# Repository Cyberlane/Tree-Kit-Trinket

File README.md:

Tree-Kit-Trinket
================

Electronic PCB Kit with a Christmas twist

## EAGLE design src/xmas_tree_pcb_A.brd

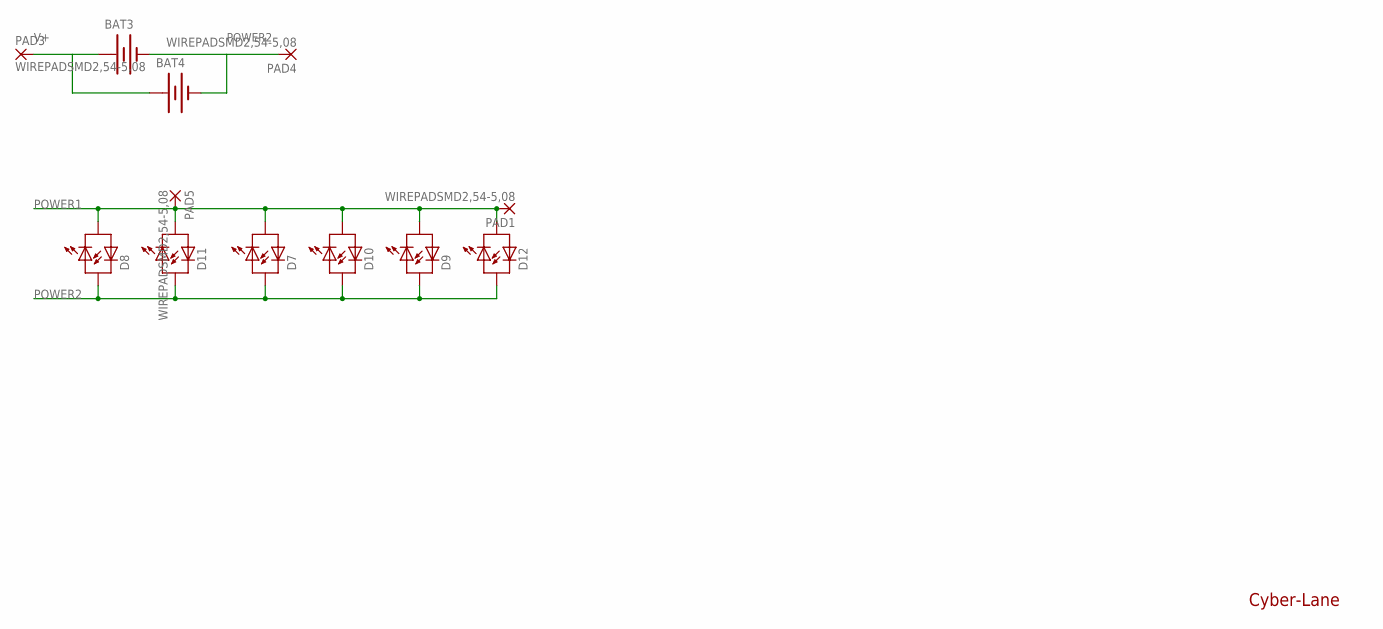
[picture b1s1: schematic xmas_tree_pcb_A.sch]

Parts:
BAT3, BAT4: BATTERY20PTH; BATTCOM_20MM_PTH
D7, D8, D9, D10, D11, D12: LED_BI_COLOR; LED3MM
PAD1, PAD3, PAD4, PAD5: WIREPADSMD2,54-5,08; SMD2,54-5,08

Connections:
POWER1: D7.K (C1), D8.K (C1), D9.K (C1), D10.K (C1), D11.K (C1), D12.K (C1), PAD1.1, PAD5.1
POWER2: BAT3.2 (-), BAT4.2 (-), D7.A (A1), D8.A (A1), D9.A (A1), D10.A (A1), D11.A (A1), D12.A (A1), PAD4.1
V+: BAT3.1 (+), BAT4.1 (+), PAD3.1

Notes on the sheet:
Cyber-Lane

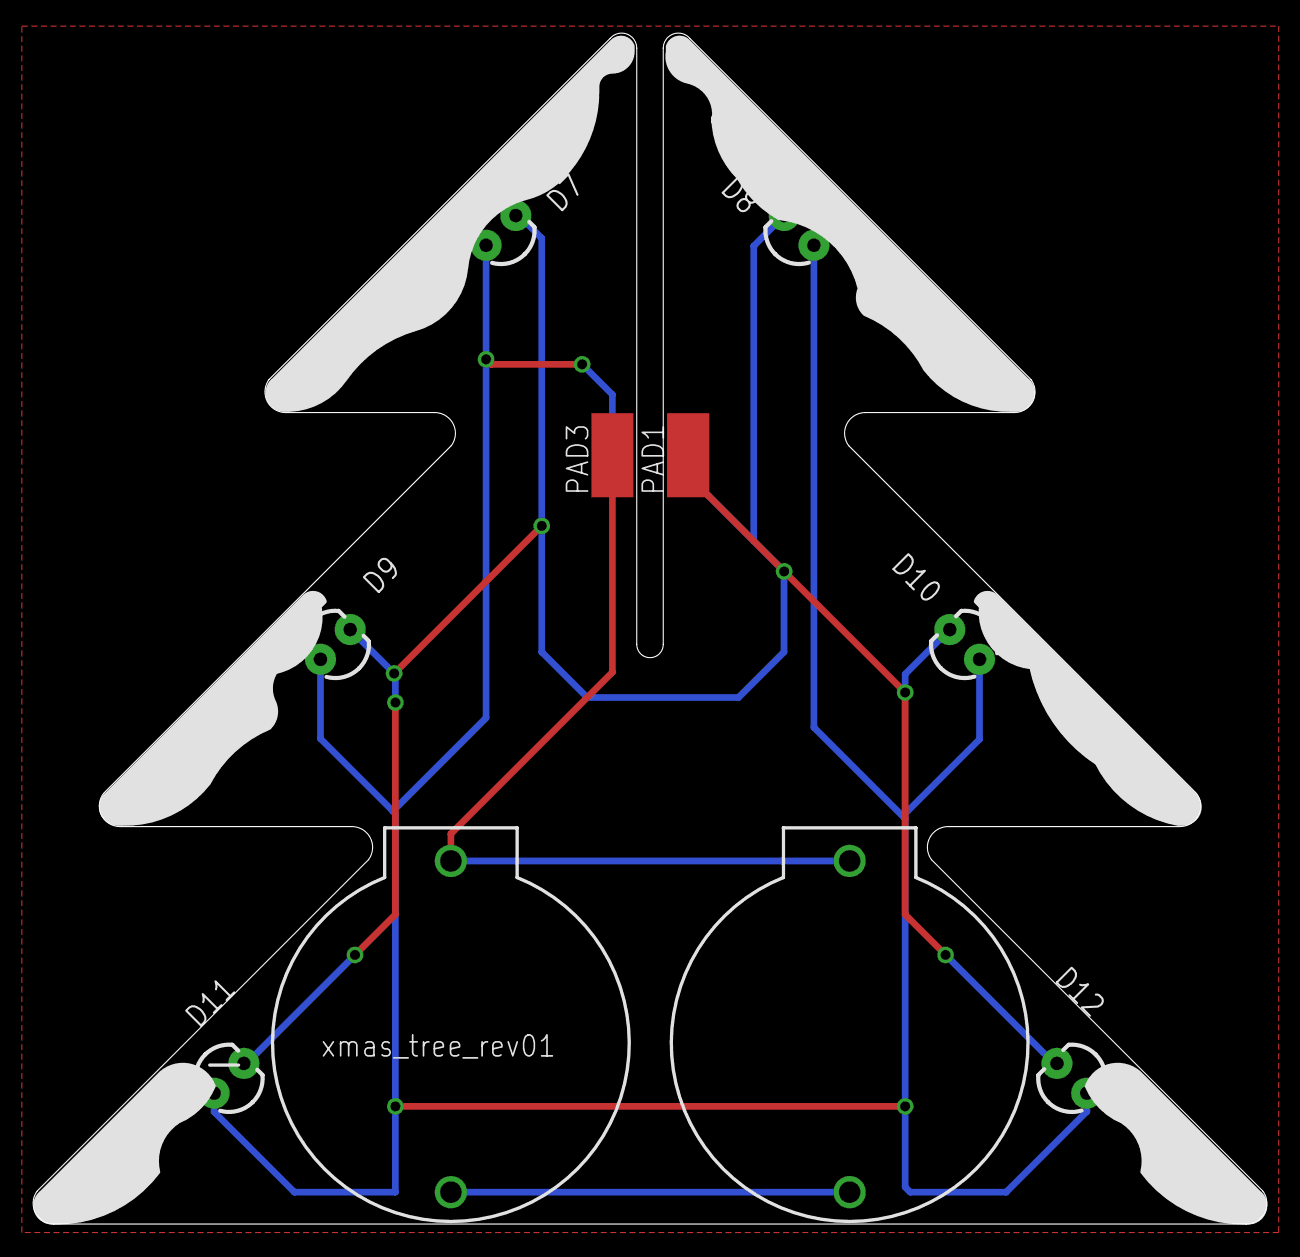
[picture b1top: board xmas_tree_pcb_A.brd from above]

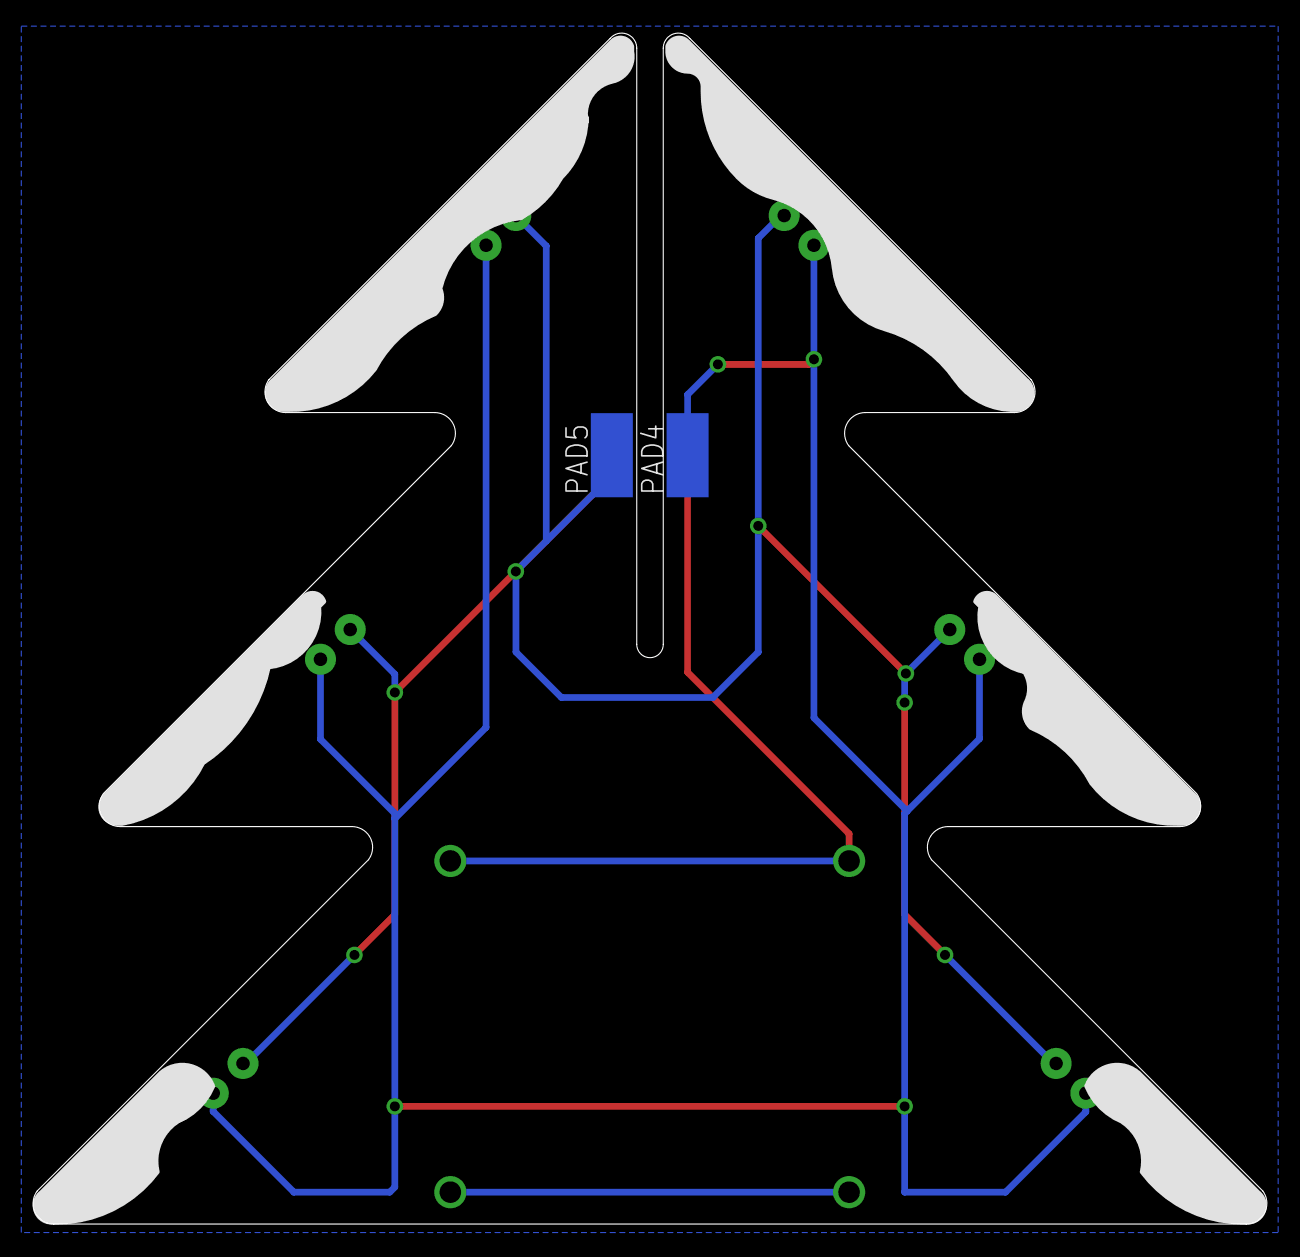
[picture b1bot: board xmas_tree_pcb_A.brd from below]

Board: 2 copper layers, 74.5 x 71.9 mm, 12 parts (2 on the bottom side), 3 nets.

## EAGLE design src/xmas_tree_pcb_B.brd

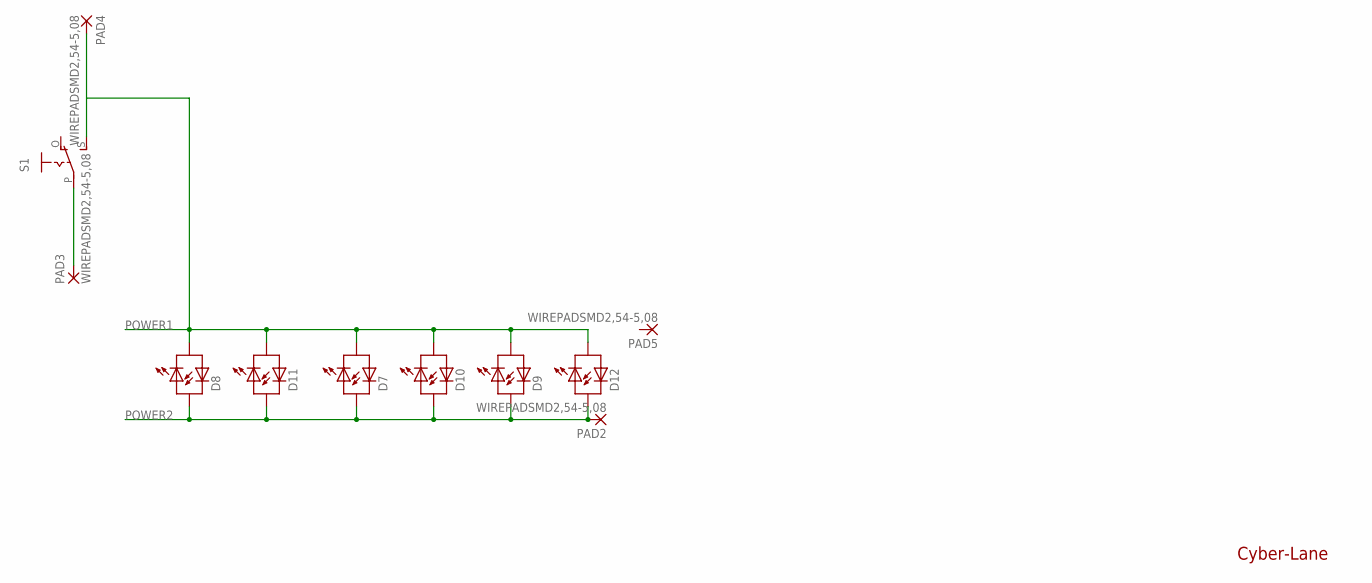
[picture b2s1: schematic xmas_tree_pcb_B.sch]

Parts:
D7, D8, D9, D10, D11, D12: LED_BI_COLOR; LED3MM
PAD2, PAD3, PAD4, PAD5: WIREPADSMD2,54-5,08; SMD2,54-5,08
S1: EG1218S; EG1218

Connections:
POWER1: D7.K (C1), D8.K (C1), D9.K (C1), D10.K (C1), D11.K (C1), D12.K (C1), PAD4.1, S1.S
POWER2: D7.A (A1), D8.A (A1), D9.A (A1), D10.A (A1), D11.A (A1), D12.A (A1), PAD2.1
V+: PAD3.1, S1.P

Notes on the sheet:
Cyber-Lane

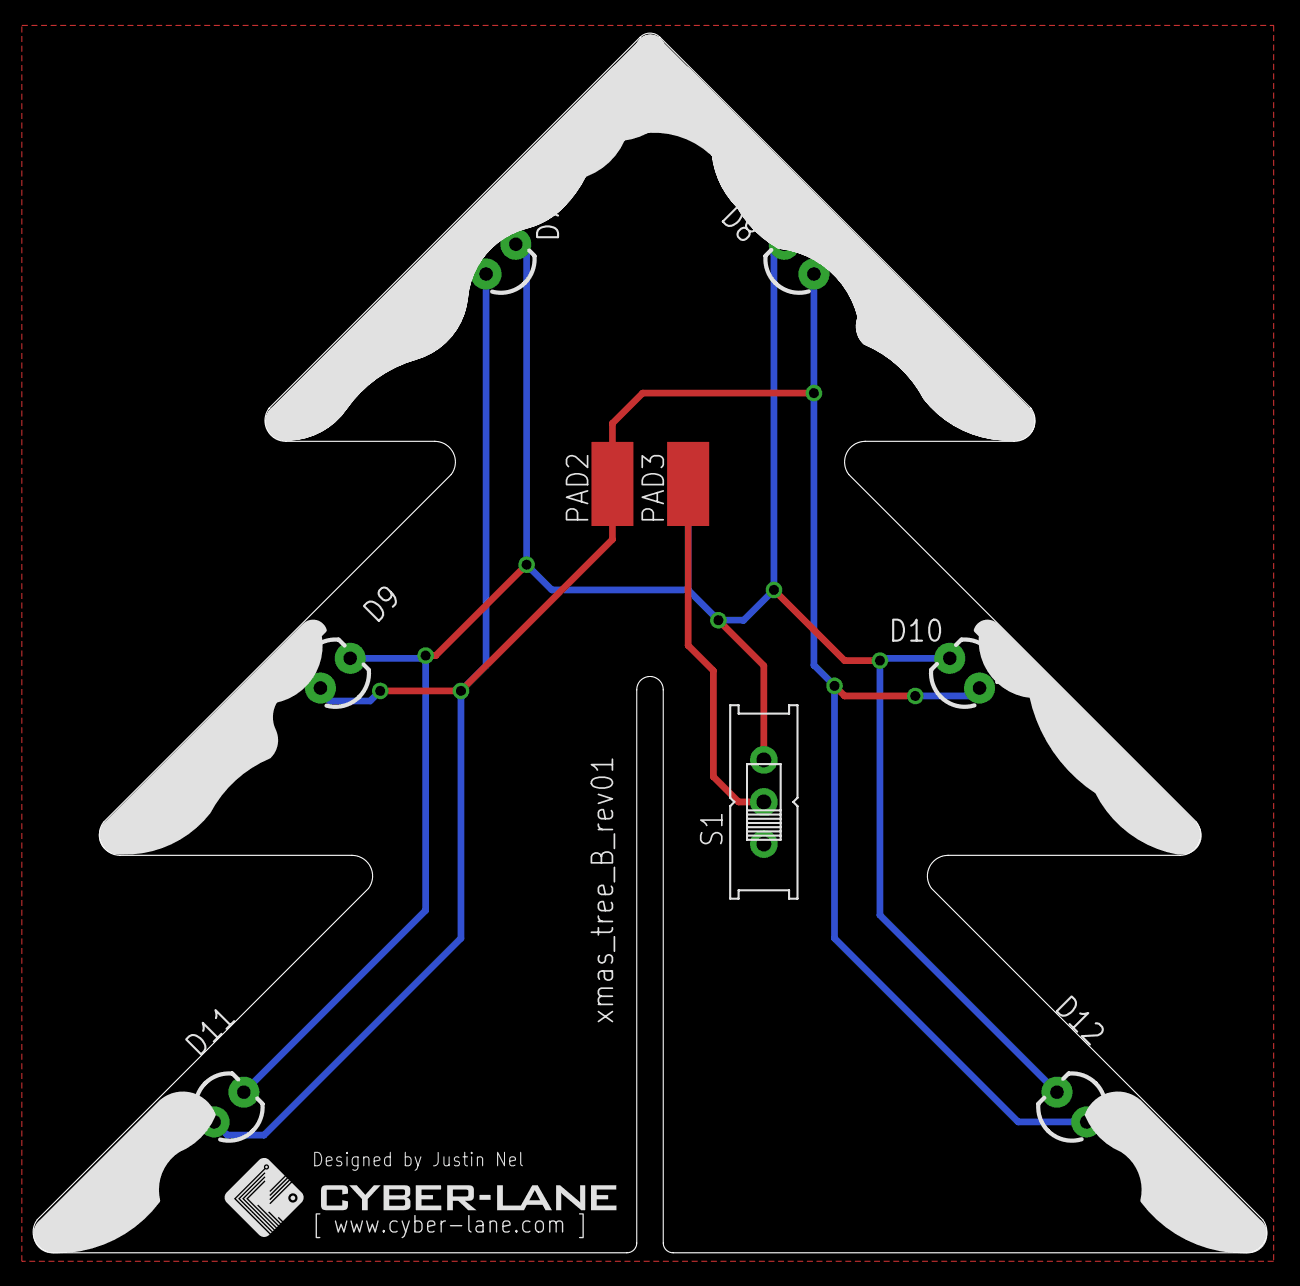
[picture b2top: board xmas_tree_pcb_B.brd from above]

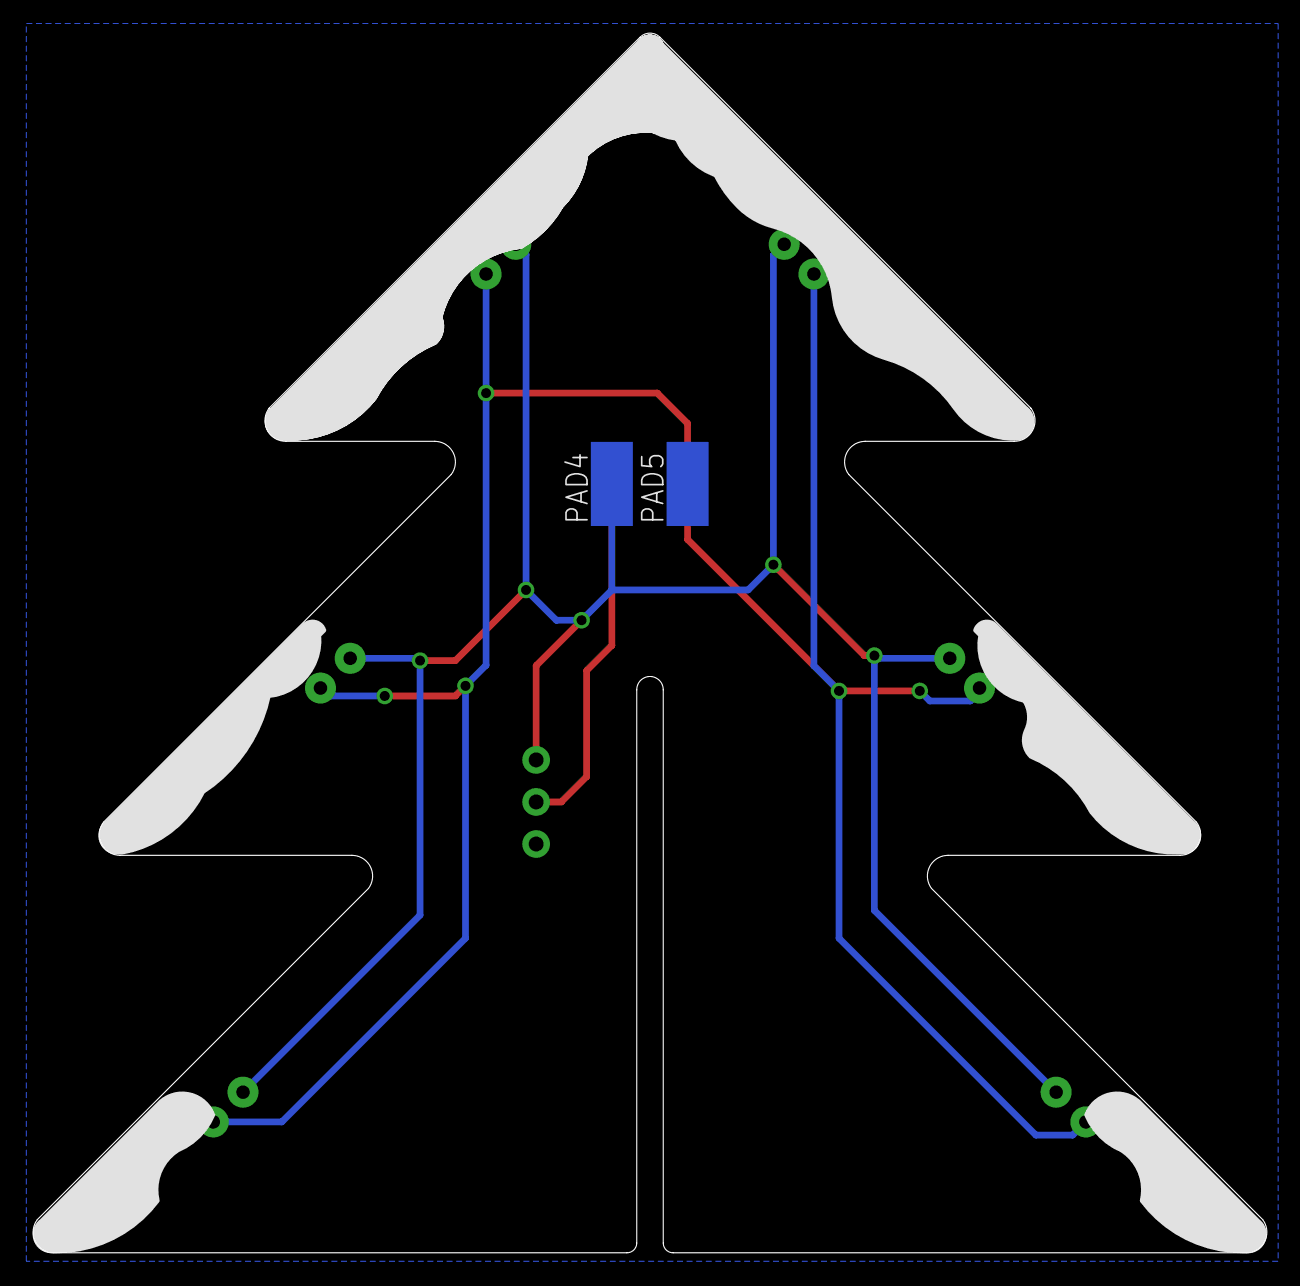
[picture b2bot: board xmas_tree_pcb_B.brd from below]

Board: 2 copper layers, 74.5 x 73.6 mm, 11 parts (2 on the bottom side), 3 nets.

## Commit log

2013-11-14 Unsorted assembly pictures
2013-11-17 Resized and cropped tutorial images
2013-11-17 Updated tutorial
2013-11-17 Fixed image links
2013-11-17 Updated images to have text overlays
2013-11-17 Fixed a typo
2013-11-17 Included how to connect and remove the batteries
2013-11-17 Updated to include packaged up kit picture

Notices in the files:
parts and their libraries:
SparkFun: Licensing: CC v3.0 Share-Alike You are welcome to use this library for commercial purposes.
